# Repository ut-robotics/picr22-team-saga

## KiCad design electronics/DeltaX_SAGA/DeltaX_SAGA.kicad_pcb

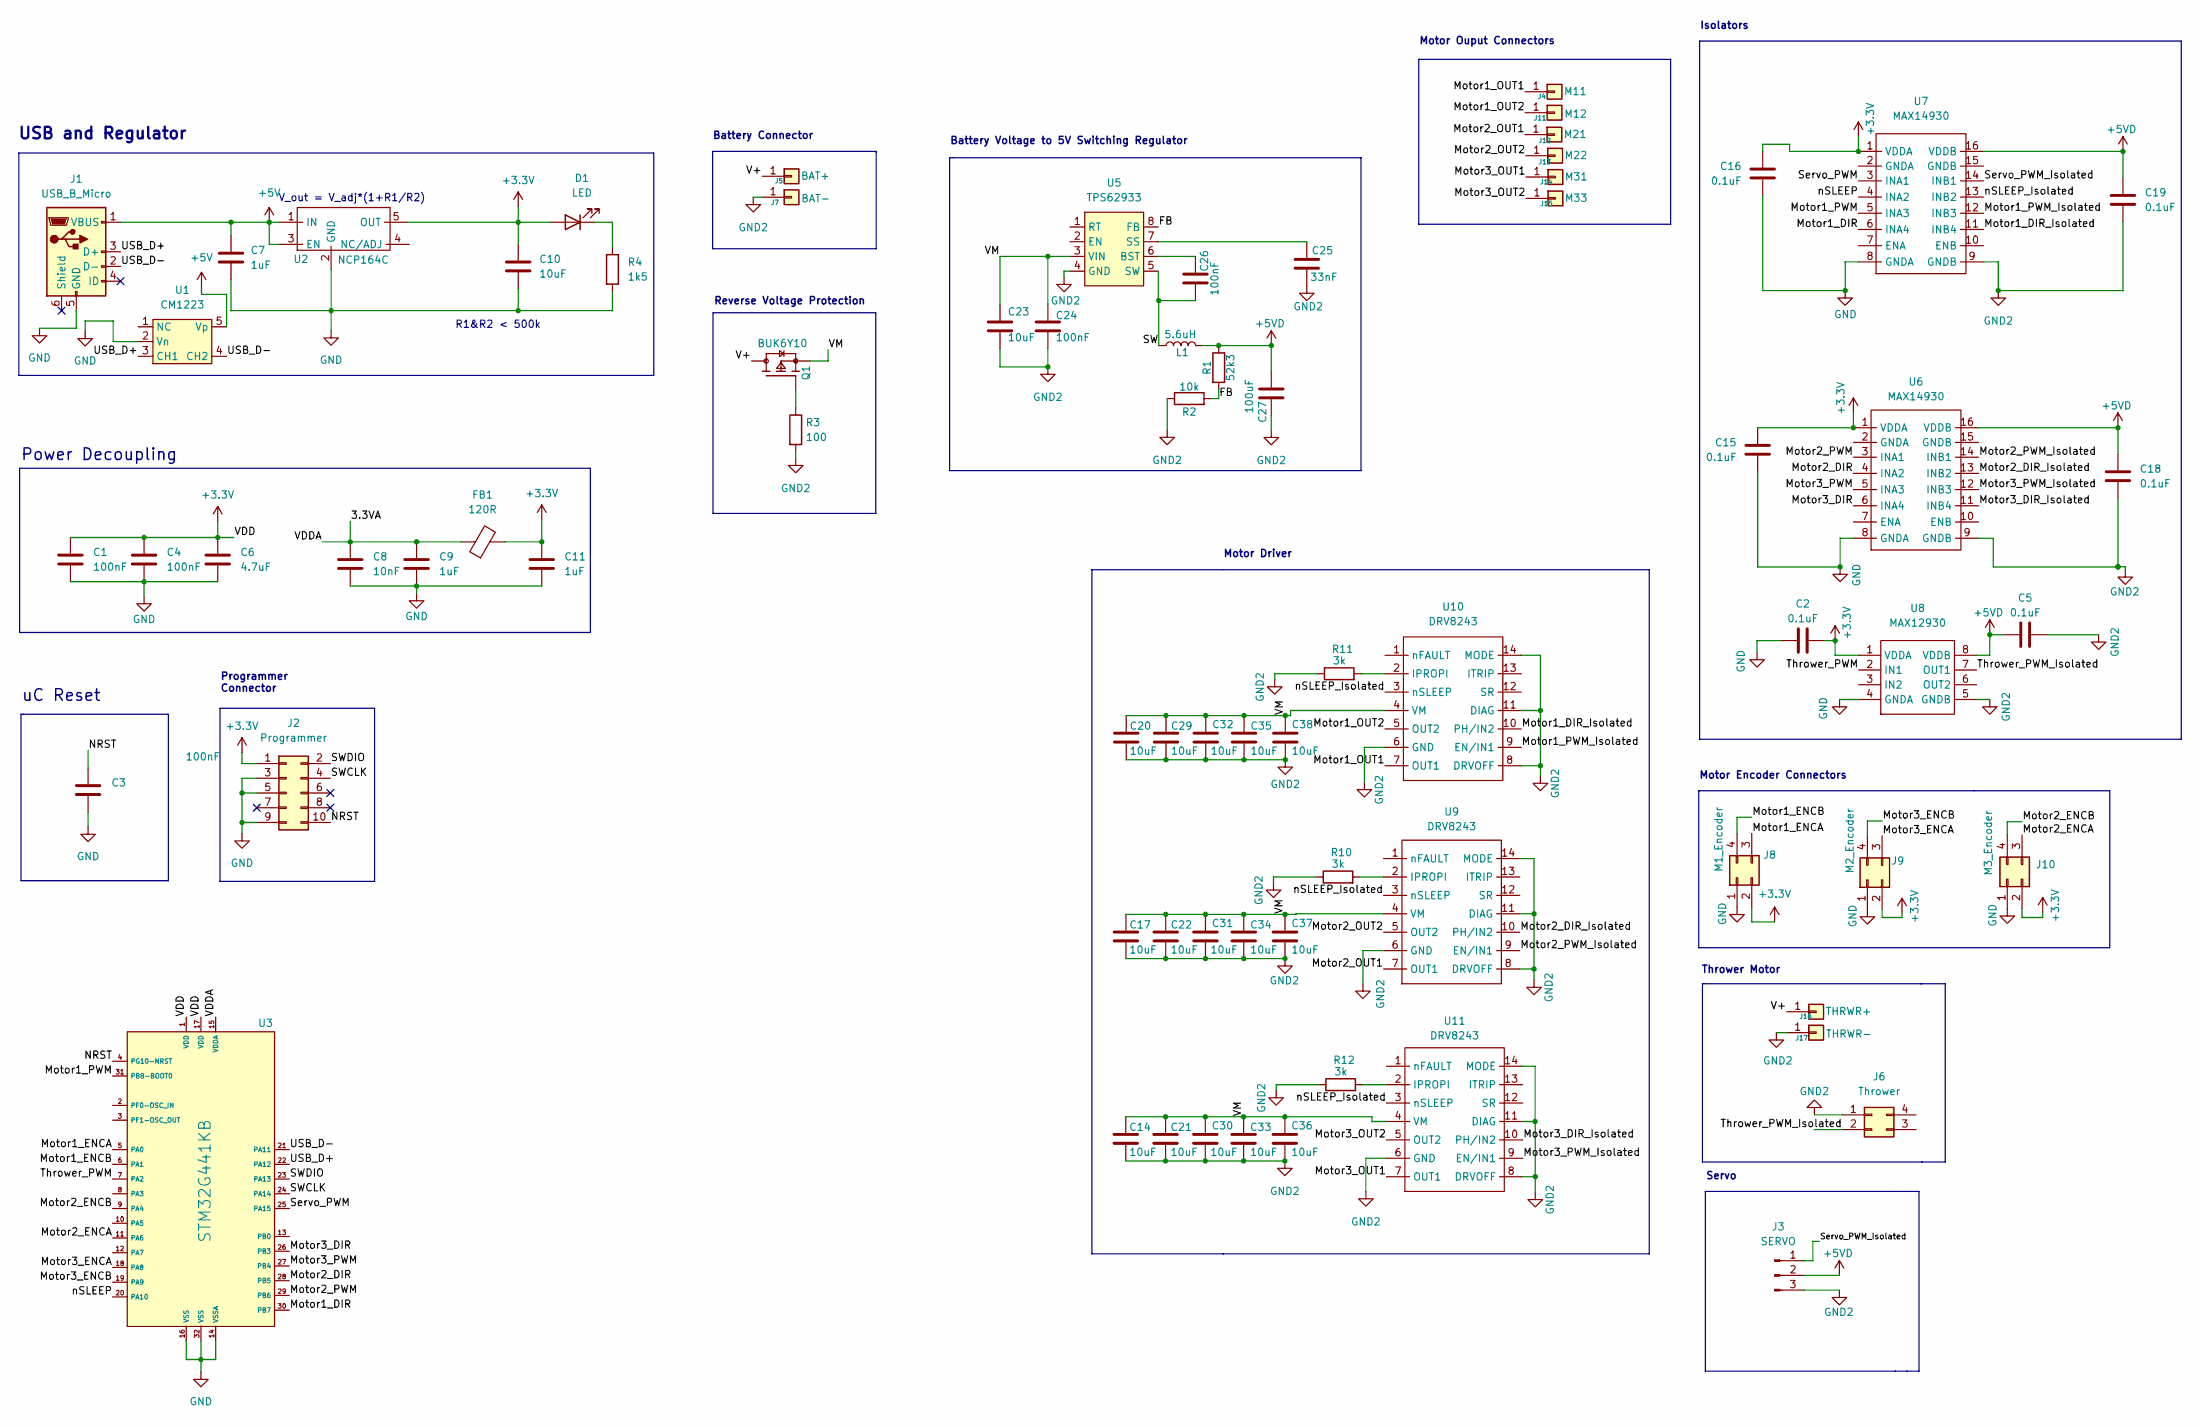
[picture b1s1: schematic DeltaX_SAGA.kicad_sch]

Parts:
C1, C3, C4, C24, C26: 100nF; C_0603_1608Metric
C2, C5, C15, C16, C18, C19: 0.1uF; C_0603_1608Metric
C6: 4.7uF; C_0603_1608Metric
C7, C9, C11: 1uF; C_0603_1608Metric
C8: 10nF; C_0603_1608Metric
C10, C14, C17, C20, C21, C22, C23, C29, C30, C31, C32, C33, C34, C35, C36, C37, C38: 10uF; C_0805_2012Metric
C25: 33nF; C_0603_1608Metric
C27: 100uF; C_1206_3216Metric
D1: LED; LED_0603_1608Metric
FB1: 120R; L_0603_1608Metric
J1: USB_B_Micro; FCI_10118193-0001LF
J2: Programmer; SAMTEC_FTSH-105-XX-X-DV
J3: SERVO; PinHeader_1x03_P2.54mm_Vertical
J4: M11; 1PinSMD
J5: BAT+; 1PinSMD
J6: Thrower; TE_7-215079-4
J7: BAT-; 1PinSMD
J8: M1_Encoder; TE_7-215079-4
J9: M2_Encoder; TE_7-215079-4
J10: M3_Encoder; TE_7-215079-4
J11: M12; 1PinSMD
J12: M21; 1PinSMD
J13: M22; 1PinSMD
J14: M31; 1PinSMD
J15: M33; 1PinSMD
J16: THRWR+; 1PinSMD
J17: THRWR-; 1PinSMD
L1: 5.6uH; SRP6060FA5R6M
Q1: BUK6Y10; TO127P600X120-5N
R1: 52k3; R_0603_1608Metric
R2: 10k; R_0603_1608Metric
R3: 100; R_0603_1608Metric
R4: 1k5; R_0603_1608Metric
R10, R11, R12: 3k; R_0603_1608Metric
U1: CM1223; SOT95P280X145-5N
U2: NCP164C; SOP95P275X110-5N
U3: STM32G441KB
U5: TPS62933
U6, U7: MAX14930; MAX14930DASE+
U8: MAX12930; MAX12930EASA+
U9, U10, U11: DRV8243

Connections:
+3.3V: C1.1, C2.2, C4.1, C6.1, C10.1, C11.1, C15.2, C16.2, D1.2 (A), FB1.2, J2.1, J8.2, J9.2, J10.2, U2.5 (OUT), U3.1 (VDD), U3.17 (VDD), U6.1 (VDDA), U7.1 (VDDA), U8.1 (VDDA)
+5V: C7.1, J1.1 (VBUS), U1.5 (Vp), U2.1 (IN), U2.3 (EN)
+5VD: C5.1, C18.2, C19.2, C27.2, J3.2, L1.2, R1.1, U6.16 (VDDB), U7.16 (VDDB), U8.8 (VDDB)
/3.3VA: C8.1, C9.1, FB1.1, U3.15 (VDDA)
/FB: R1.2, R2.2, U5.8 (FB)
/Motor1_DIR: U3.30 (PB7), U7.6 (INA4)
/Motor1_DIR_Isolated: U7.11 (INB4), U10.10 (PH/IN2)
/Motor1_ENCA: J8.3, U3.5 (PA0)
/Motor1_ENCB: J8.4, U3.6 (PA1)
/Motor1_OUT1: J4.1, U10.7 (OUT1)
/Motor1_OUT2: J11.1, U10.5 (OUT2)
/Motor1_PWM: U3.31 (PB8-BOOT0), U7.5 (INA3)
/Motor1_PWM_Isolated: U7.12 (INB3), U10.9 (EN/IN1)
/Motor2_DIR: U3.28 (PB5), U6.4 (INA2)
/Motor2_DIR_Isolated: U6.13 (INB2), U9.10 (PH/IN2)
/Motor2_ENCA: J10.3, U3.11 (PA6)
/Motor2_ENCB: J10.4, U3.9 (PA4)
/Motor2_OUT1: J12.1, U9.7 (OUT1)
/Motor2_OUT2: J13.1, U9.5 (OUT2)
/Motor2_PWM: U3.29 (PB6), U6.3 (INA1)
/Motor2_PWM_Isolated: U6.14 (INB1), U9.9 (EN/IN1)
/Motor3_DIR: U3.26 (PB3), U6.6 (INA4)
/Motor3_DIR_Isolated: U6.11 (INB4), U11.10 (PH/IN2)
/Motor3_ENCA: J9.3, U3.18 (PA8)
/Motor3_ENCB: J9.4, U3.19 (PA9)
/Motor3_OUT1: J14.1, U11.7 (OUT1)
/Motor3_OUT2: J15.1, U11.5 (OUT2)
/Motor3_PWM: U3.27 (PB4), U6.5 (INA3)
/Motor3_PWM_Isolated: U6.12 (INB3), U11.9 (EN/IN1)
/NRST: C3.1, J2.10, U3.4 (PG10-NRST)
/SW: C26.2, L1.1, U5.5 (SW)
/SWCLK: J2.4, U3.24 (PA14)
/SWDIO: J2.2, U3.23 (PA13)
/Servo_PWM: U3.25 (PA15), U7.3 (INA1)
/Servo_PWM_Isolated: J3.1, U7.14 (INB1)
/Thrower_PWM: U3.7 (PA2), U8.2 (IN1)
/Thrower_PWM_Isolated: J6.2, U8.7 (OUT1)
/USB_D+: J1.3 (D+), U1.3 (CH1), U3.22 (PA12)
/USB_D-: J1.2 (D-), U1.4 (CH2), U3.21 (PA11)
/V+: J5.1, J16.1, Q1.5 (D)
/VM: C14.1, C17.1, C20.1, C21.1, C22.1, C23.1, C24.1, C29.1, C30.1, C31.1, C32.1, C33.1, C34.1, C35.1, C36.1, C37.1, C38.1, Q1.1 (S), Q1.2, Q1.3, U5.3 (VIN), U9.4 (VM), U10.4 (VM), U11.4 (VM)
/nSLEEP: U3.20 (PA10), U7.4 (INA2)
/nSLEEP_Isolated: U7.13 (INB2), U9.3 (nSLEEP), U10.3 (nSLEEP), U11.3 (nSLEEP)
GND: C1.2, C2.1, C3.2, C4.2, C6.2, C7.2, C8.2, C9.2, C10.2, C11.2, C15.1, C16.1, J1.5 (GND), J2.3, J2.5, J2.9, J8.1, J9.1, J10.1, R4.2, U1.2 (Vn), U2.2 (GND), U3.14 (VSSA), U3.16 (VSS), U3.32 (VSS), U6.8 (GNDA), U7.8 (GNDA), U8.4 (GNDA)
GND2: C5.2, C14.2, C17.2, C18.1, C19.1, C20.2, C21.2, C22.2, C23.2, C24.2, C25.2, C27.1, C29.2, C30.2, C31.2, C32.2, C33.2, C34.2, C35.2, C36.2, C37.2, C38.2, J3.3, J6.1, J7.1, J17.1, R2.1, R3.2, R10.1, R11.1, R12.1, U5.4 (GND), U6.9 (GNDB), U7.9 (GNDB), U8.5 (GNDB), U9.6 (GND), U9.8 (DRVOFF), U9.11 (DIAG), U9.14 (MODE), U10.6 (GND), U10.8 (DRVOFF), U10.11 (DIAG), U10.14 (MODE), U11.6 (GND), U11.8 (DRVOFF), U11.11 (DIAG), U11.14 (MODE)
unnamed: C25.1, U5.7 (SS)
unnamed: C26.1, U5.6 (BST)
unnamed: D1.1 (K), R4.1
unnamed: Q1.4 (G), R3.1
unnamed: R10.2, U9.2 (IPROPI)
unnamed: R11.2, U10.2 (IPROPI)
unnamed: R12.2, U11.2 (IPROPI)

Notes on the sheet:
Power Decoupling
Isolators
USB and Regulator
Motor Driver
Servo
Motor Encoder Connectors
Reverse Voltage Protection
uC Reset
Battery Connector
Battery Voltage to 5V Switching Regulator
R1&R2 < 500k
Motor Ouput Connectors
V_out = V_adj*(1+R1/R2)
Thrower Motor
Programmer Connector

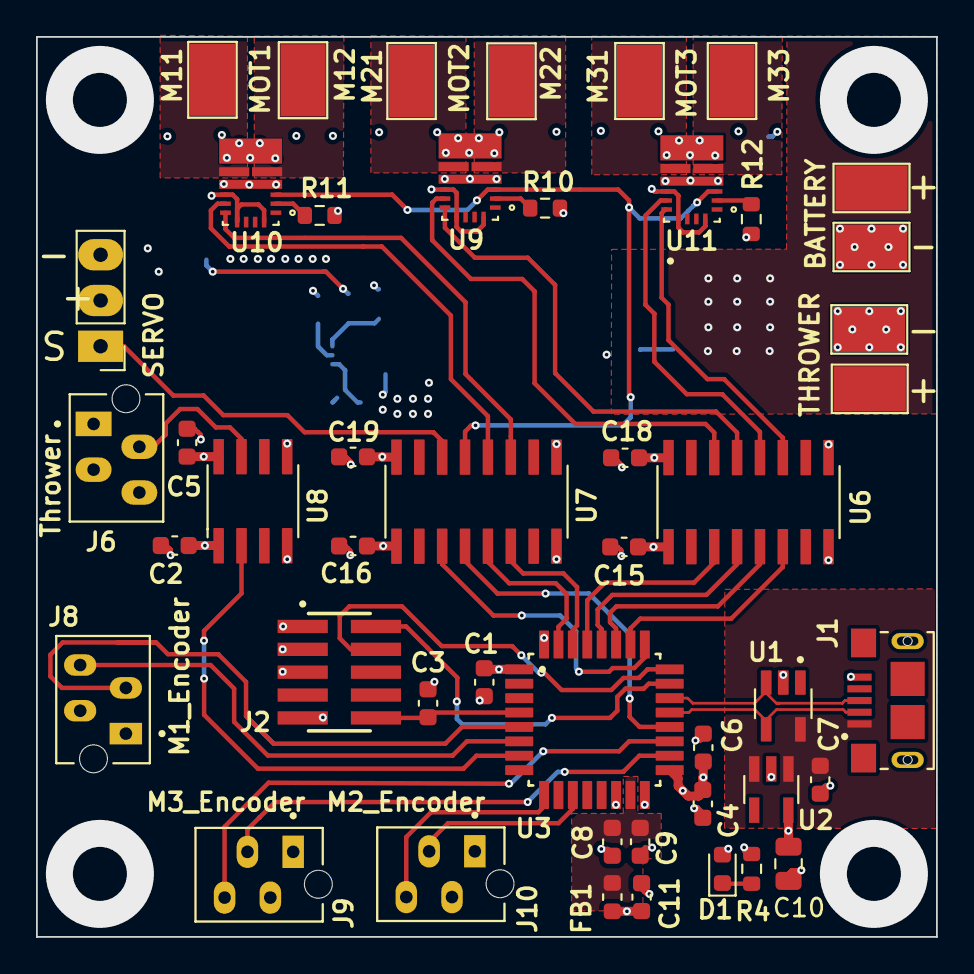
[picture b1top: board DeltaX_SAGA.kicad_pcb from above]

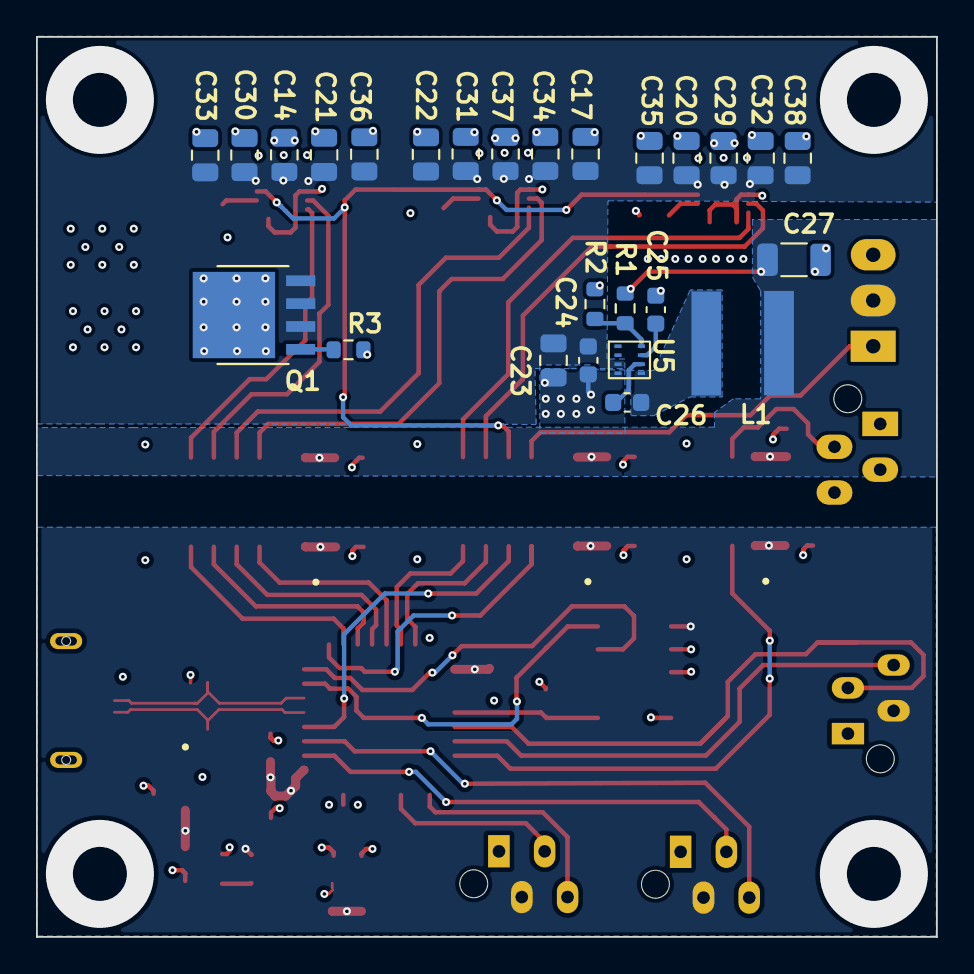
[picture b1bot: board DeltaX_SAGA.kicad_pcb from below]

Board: 4 copper layers, 50.0 x 50.0 mm, 73 parts (30 on the bottom side), 52 nets.

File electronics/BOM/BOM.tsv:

Name	Designator	Quantity	Description	Mouser Order Code	Farnell Order Code	TME Order Code
10nF	C8	1	Multilayer Ceramic Capacitors MLCC - SMD/SMT CGA 0603 50V 0.01uF X7R 10% AEC-Q200	810-CGA3E2X7R1H103K	CA07638	N/A
33nF	C25	1	Multilayer Ceramic Capacitors MLCC - SMD/SMT 0402 50VDC 0.033uF 10% X7R	963-MAASU105SB7333KF	1740618	06035C333JAT2A
100nF	C1, C3, C4, C24, C26	5	Multilayer Ceramic Capacitors MLCC - SMD/SMT 0402 50VDC 0.1uF 10% X7R AEC-Q200	963-UMK105B7104KVHF	0603B104J500CT	2332586
0.1uF	C2, C5, C15, C16, C18, C19	6	Multilayer Ceramic Capacitors MLCC - SMD/SMT 0402 50VDC 0.1uF 10% X7R AEC-Q200	963-UMK105B7104KVHF	CC0603KRX7R8BB104	1740614
4.7uF	C6	1	Multilayer Ceramic Capacitors MLCC - SMD/SMT 0603 10VDC 4.7uF 10% X7T AEC-Q200	810-CGA3E1X7T1A475AC	N/A	N/A
10uF	C10, C14, C17, C20, C21, C22, C23, C29, C30, C31, C32, C33, C34, C35, C36, C37, C28	17	Multilayer Ceramic Capacitors MLCC - SMD/SMT 10uF, 25V, 10%, X6S, 0805 Multi-layer Ceramic Capacitor	187-CL21X106KAYQNWE	C2012X5R1E106KAB	2346927
100uF	C27	1	Multilayer Ceramic Capacitors MLCC - SMD/SMT 1206 6.3VDC 100uF 20% X5R	963-JMK316BJ107ML-T	3922223	N/A
LED	D1	1	LED Uni-Color Green 565nm 2-Pin Chip LED T/R, LED GREEN CLEAR CHIP SMD	859-LTST-C190GKT	LTST-C190GKT	1465991
120R	FB1	1	Ferrite Beads BMC 0603 120R 25% A Gen C	279-BMC1JY0120AN	N/A	N/A
USB_B_Micro	J1	1	USB - micro B USB 2.0 Receptacle Connector 5 Position Surface Mount, Right Angle; Through Hole	649-10118193-0001LF	10118193-0001LF/C	2751675
Programmer	J2	1	Detachable Programmer connector	200-FTSH10501LDVK	N/A	N/A
SERVO	J3	1	3-pin vertical header pin 2.54mm pitch	855-M20-9770446	CN21901	N/A
M1_Encoder	J8	1	PCB Receptacle, Board-to-Board, 1.27 mm, 2 Rows, 4 Contacts, Through Hole Mount, Micro-MaTch	571-215079-4	1772996	7-215079-4
M2_Encoder	J9	1	PCB Receptacle, Board-to-Board, 1.27 mm, 2 Rows, 4 Contacts, Through Hole Mount, Micro-MaTch	571-215079-4	1772996	7-215079-4
M3_Encoder	J10	1	PCB Receptacle, Board-to-Board, 1.27 mm, 2 Rows, 4 Contacts, Through Hole Mount, Micro-MaTch	571-215079-4	1772996	7-215079-4
Thrower	J6	1	PCB Receptacle, Board-to-Board, 1.27 mm, 2 Rows, 4 Contacts, Through Hole Mount, Micro-MaTch	571-215079-4	1772996	7-215079-4
5.6 uH	L1	1	Power Inductor (SMD), 5.6 µH, 10 A, Shielded, 10 A, SRP6060FA	652-SRP6060FA-5R6M	2901832	N/A
BUK6Y10	Q1	1	BUK6Y10-30P	771-BUK6Y10-30PX	BUK6Y10-30PX	3438512
100	R3	1	Thick Film Resistors - SMD 100 Ohms 200 mW 0603 5%	603-RC0603JR-7W100RL	N/A	N/A
1k5	R4	1	Thick Film Resistors - SMD 1/10watt 1.5Kohms 5%	71-CRCW0603J-1.5K-E3	N/A	0603SAF1501T5E
3k	R10, R11, R12	3	Chip Resistor, 0 Ohm, Jumper, 100 mW, -55 to 155 degC, 0603 (1608 Metric), RoHS, Tape and Reel	667-ERJ-UP3F3301V	ERA3AEB332V	9238549
10k	R3	1	Chip Resistor, 0 Ohm, Jumper, 100 mW, -55 to 155 degC, 0603 (1608 Metric), RoHS, Tape and Reel	603-RT0603FRE0710KL	CRGP0603F10K	2073356
52k3	R1 	1	52.3 kOhm, SMD 0603	667-ERJ-3EKF5232V	2059474	ERJ3EKF5232V
CM1223	U1	1	Industry First Low Capacitance ESD Protection Arrays with Backdrive Protection, 5-Pin SOT- 23	748-CM1223-02SO	3607672	CM1223-02SO
NCP164C	U2	1	LDO Voltage Regulators LDO 300mA AD 3.3V	863-NCP164CSN330T1G	3367831	NCP164CSN330T1G
STM32G441KB	U3	1	ARM MCU, STM32 Family STM32G4 Series Microcontrollers, ARM Cortex-M4F, 32 bit, 170 MHz, 128 KB	511-STM32G441KBT6	3132413	N/A
TPS62933	U5	1	Switching Voltage Regulators 3.8-V to 30-V, 3-A, 200-kHz to 2.2-MHz, low-IQ synchronous buck converter in SOT-583 package	595-TPS62933DRLR	N/A	N/A
MAX14930	U6, U7	1	Digital Isolator, 4 Channel, 38.2 ns, 1.71 V, 5.5 V, NSOIC, 16 Pins	700-MAX14930AASE+	3918113	N/A
MAX12930	U8	1	Digital Isolator, 2 Channel, 23.9 ns, 1.71 V, 5.5 V, NSOIC, 8 Pins	700-MAX12930EASA+	3918086	N/A
DRV8243	U9, U10, U11	3	Automotive 40-V, 12-A H-Bridge driver with integrated current sensing and feedback 14-VQFN-HR -40 to 125	595-DRV8243HQRXYRQ1	N/A	N/A

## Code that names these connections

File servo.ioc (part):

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Mcu.Name=STM32G431K(6-8-B)Tx
Mcu.Package=LQFP32
Mcu.UserName=STM32G431KBTx
PA0.GPIOParameters=GPIO_Label
PA0.GPIO_Label=M1_ENCA
PA0.Signal=S_TIM2_CH1
PA1.GPIOParameters=GPIO_Label
PA1.GPIO_Label=M1_ENCB
PA1.Signal=S_TIM2_CH2
PA10.GPIOParameters=GPIO_Label
PA10.GPIO_Label=nSleep
PA10.Signal=GPIO_Output
PA11.Mode=Device
PA11.Signal=USB_DM
PA12.Mode=Device
PA12.Signal=USB_DP
PA13.GPIOParameters=GPIO_Label
PA13.GPIO_Label=T_SWDIO
PA13.Mode=Serial_Wire
PA13.Signal=SYS_JTMS-SWDIO
PA14.GPIOParameters=GPIO_Label
PA14.GPIO_Label=T_SWCLK
PA14.Mode=Serial_Wire
PA14.Signal=SYS_JTCK-SWCLK
PA15.GPIOParameters=GPIO_Label
PA15.GPIO_Label=Servo_PWM
PA15.Signal=S_TIM8_CH1
PA2.GPIOParameters=GPIO_Label
PA2.GPIO_Label=Thrower_PWM
PA2.Signal=S_TIM15_CH1
PA4.GPIOParameters=GPIO_Label
PA4.GPIO_Label=M2_ENCB
PA4.Signal=S_TIM3_CH2
PA6.GPIOParameters=GPIO_Label
PA6.GPIO_Label=M2_ENCA
PA6.Signal=S_TIM3_CH1
PA8.GPIOParameters=GPIO_Label
PA8.GPIO_Label=M3_ENCA
PA8.Signal=S_TIM1_CH1
PA9.GPIOParameters=GPIO_Label
PA9.GPIO_Label=M3_ENCB
PA9.Signal=S_TIM1_CH2
PB3.GPIOParameters=GPIO_Label
PB3.GPIO_Label=M3_DIR
PB3.Signal=GPIO_Output
PB4.GPIOParameters=GPIO_Label
PB4.GPIO_Label=M3_PWM
PB4.Signal=S_TIM16_CH1
PB5.GPIOParameters=GPIO_Label
PB5.GPIO_Label=M2_DIR
PB5.Signal=GPIO_Output
PB6.GPIOParameters=GPIO_Label
PB6.GPIO_Label=M2_PWM
PB6.Signal=S_TIM4_CH1
PB7.GPIOParameters=GPIO_Label
PB7.GPIO_Label=M1_DIR
PB7.Signal=GPIO_Output
PB8-BOOT0.GPIOParameters=GPIO_Label
PB8-BOOT0.GPIO_Label=M1_PWM
PB8-BOOT0.Signal=S_TIM4_CH3
PF0-OSC_IN.GPIOParameters=GPIO_Label
PF0-OSC_IN.GPIO_Label=M1_DIR_1
PF0-OSC_IN.Signal=GPIO_Output
PF1-OSC_OUT.GPIOParameters=GPIO_Label
PF1-OSC_OUT.GPIO_Label=M1_DIR_2
PF1-OSC_OUT.Signal=GPIO_Output
RCC.HSE_VALUE=8000000
RCC.SYSCLKFreq_VALUE=160000000
RCC.SYSCLKSource=RCC_SYSCLKSOURCE_PLLCLK
board=NUCLEO-G431KB
boardIOC=true

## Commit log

2022-09-07 Initialize software
2022-09-07 Initialize documentation
2022-09-07 Initialize firmware
2022-09-07 Initialize electronics
2022-09-11 initial schematic design(without thrower)
2022-09-11 design of necessary symbols
2022-09-11 screenshot of the schematic design till date
2022-09-11 initial schematic updated
2022-09-11 screenshot of updated schematic added
2022-09-11 backups for schematic added
2022-09-15 schematic updated
2022-09-15 new symbol libraries added
2022-09-15 backup files added
2022-09-15 schematic annotated and some components assigned
2022-09-15 renamed the schematic library directory
2022-09-15 Footprint libaries directory created with necessary footprints
2022-09-15 previous unnecessary files removed
2022-09-15 motor driver footprint added
2022-09-18 updated the team page and blog from my side
2022-09-18 updated the boardc schematic and pcb design
2022-09-18 libraries updated
2022-09-18 team page updated
2022-09-18 updated the readme file
2022-09-18 added backup files
2022-09-18 README from this branch omitted
2022-09-19 team page with blog added
2022-09-29 Schematic board updated
2022-09-29 PCB design updated
2022-09-29 PCB dsign updated
2022-09-29 cache
2022-09-29 PCB design updated with fill zones
2022-09-30 Updated library for DRV8243
2022-09-30 Updated library MAX12930
2022-09-30 Updated library for MAX14930
2022-09-30 Updated library for NCP164C
2022-09-30 Updated PCB board
2022-09-30 added cache files
2022-09-30 Added the backup files
2022-09-30 PCB updated
2022-10-03 Board schematic updated
2022-10-03 added library for buck TPS62933
2022-10-03 Updated the PCB design
2022-10-03 Updated kicad files
2022-10-03 added chache files
2022-10-03 added lib-table
2022-10-03 backup file added
2022-10-03 daily log added
2022-10-10 updated the reverse voltage MSOFET footprint library
2022-10-10 added footprint library for the inductor SRP6060FA5RM
2022-10-10 updated the kicad schematic symbol for the MSOFET
2022-10-10 Updated the schematic
2022-10-10 Updated the KiCAD package
2022-10-10 updated the KiCAD prl file
2022-10-10 updated the library table
2022-10-10 Updated the symbol for TPS62933 buck
2022-10-11 complete PCB updated
2022-10-11 added a single pin solderable pad
2022-10-12 PCB design updated and complete design added
2022-10-12 updated PCB design
2022-10-13 KiCAD package updated
2022-10-13 Reverse Voltage Protection MOSFET PCB footprint updated
2022-10-17 PCB board updated
2022-10-17 updated the kciad project file
2022-10-17 Team blog from my side updated
2022-10-20 KiCAD package/s updated
2022-10-20 Footprint libraries updated
2022-10-23 Updated the PDB design
2022-10-23 KiCAD project files updated
2022-10-23 Full PCB design updated
2022-10-23 KiCAD project files added
2022-10-26 KiCAD project file updated
2022-10-26 Backup files addde
2022-10-27 PCB design added
2022-10-27 KiCAD project file/s added
2022-10-27 KiCAD files added
2022-10-27 Labels and orientations of certain components updated in schematic
2022-10-27 PCB labels updated
2022-10-28 PCB design with label optimised and updated
2022-10-28 PCB labels and routing optimised and updated
2022-10-28 PCB design updated with labels aligned
2022-10-28 KiCAD project file updatde
2022-10-30 PCB design updated with routing improvements
2022-10-30 PCB design updated with improved routing
2022-10-31 Updated PCB design with board cutouts and holes in proper grid size
2022-10-31 Updated PCB design with gerbers
2022-10-31 Gerber files added
2022-10-31 Team blog added from my(Anish) side
2022-10-31 PCB design updated with correct labels
2022-11-14 previously pads not connected reviewed and updated
2022-11-14 BNackup files added
2022-11-14 updated the team documentation README.asciidoc
2022-11-14 updated the team documentation
2022-12-08 directory boilerplate files
2022-12-08 instances for camera api and test files added
2022-12-08 enum class for color for specific objects added
2022-12-08 python code for configuring color for various objects added
2022-12-08 pythin aoi for image processing added
2022-12-08 api.py file for driving motors and thrower methods added
2022-12-08 requirements.txt added
2022-12-08 code for task: mainboard communication added
2022-12-08 code for streaming video from the camer added
2022-12-08 code for the task: find a ball added
2022-12-08 code for the task: follow a ball added
2022-12-10 python setup removed
2022-12-10 requirements file removed
2022-12-12 removed unnecessary files
2022-12-12 Finding a serial port code added
2022-12-12 updated with the new api.py file for serial port finding
2022-12-12 updated the code fetching the frame size from camera object
2022-12-12 variable nomenclature made consitent
2022-12-12 raise exception when USB com port not found
2022-12-12 states for state machine logic
2022-12-12 updated the USB port dynamic search
2022-12-12 updated the code with frame size from camera object
2022-12-12 added testing state machine for manual mode
2022-12-12 enum class with states added
2022-12-12 testing the state machine implementation
2022-12-12 added the progress and team documentation from my side
2022-12-12 updated the mainboard communication with state machine implementation
2022-12-12 updated the dynamic searching of the USB device
2022-12-12 changed the largest ball variable using already sorted processed_ball from image_processor
2022-12-12 updated the iamge processor file
2022-12-12 updated the mainboard communication program withs tate machine logic to drive forward on speed commands
2022-12-12 added the incomplete code for finding and following the ball using state machine logic
2022-12-12 updated the code with try except block
2022-12-12 initial
2022-12-12 updated the largest processed ball with alerady sorted list from image processor
2022-12-13 state machine functions added
2022-12-13 main file for all taks combnined
2022-12-13 finding the ball program updated
2022-12-13 video streaming program wiht the largest ball fetched from processed data list without max filtering
2022-12-13 main program with the largest ball fetched from processed data list without max filtering
2022-12-13 state machine logic implementation with updated ball location for following
2022-12-13 added the function to turn when there is no ball
2022-12-13 updated the code removing assigning states and calls functions from state_machine.py
2022-12-13 refactored the code ommiting the redundant codes
2022-12-13 updated the state machine code which takes the entire processed data as input
2022-12-13 updated the code to send entire processed data frame as input to state machine code
2022-12-13 passed the frame resolution ubsing the camera object
2022-12-13 updated the current state function with frame resolution passed from main.py
2022-12-13 passed the camera resolution parameters in the constructor class of the state machine call
2022-12-13 updated the state machine code with camera resolution parameters in the constructor
2022-12-13 minor tweaks
2022-12-15 fixes and add PID back propagation control
2022-12-16 fix PID
2022-12-21 code cleanup
2022-12-21 cmake bug fix
2022-12-21 commented code remover
2022-12-21 fix for new robot change 1 and 3 encoders
2023-01-13 BOM file added
2023-01-13 schematic PDF added
2023-01-13 PCB 3D views with annotations and labels added
2023-01-13 electronics documentation updated
2023-01-13 front PCB image updated
2023-01-14 software documentation added
2023-01-14 software documentation updated
2023-01-14 added section frames for documentation
2023-01-14 PCB front and back 3D images with annotations and labels added
2023-01-14 Electronics Design documentation added
2023-01-14 PCB images front and back with annotations and labels
2023-01-14 removinf unnecessary files
2023-01-14 flow chart added
2023-01-14 programming documentation updated with flow charts
2023-01-14 programming documentation updated
2023-01-14 added all necessary images
2023-01-14 Team documentation updated
2023-01-14 removed few images
2023-01-14 PCB front and back 3D view added
2023-01-14 added mechanics pictures
2023-01-14 replacing the state machine logic
2023-01-14 updated the robot states with DRIVE_TO_OTHER_HALF state
2023-01-14 updated the state machine logic with an additional state of driving to other half
2023-01-14 updated mechanics readme
2023-01-14 updated the electronics documentation
2023-01-14 removing redundant files
2023-01-14 updated the mechanics documentation
2023-01-14 updated team documentation
2023-01-14 removing outdated state machine flow chart
2023-01-14 added the updated state machine flow chart
2023-01-14 added fusion assembly link
2023-01-14 removing outdated state machine work flow
2023-01-14 fusion assembly link
2023-01-14 added the new state machine work flow
2023-01-14 removing the outdated state machine work flow
2023-01-14 updated state_machine_workflow added
2023-01-14 updated the team documentation with updated state machine logic
2023-01-14 added self analysis
2023-01-14 updated personal comments
2023-01-14 fixed formatting issues
2023-01-14 electronics documentation added
2023-01-14 removed previous BOM
2023-01-14 updated the BOM
2023-01-15 Team documentation updated correcting issues
2023-01-15 added software/README inside the software folder
2023-01-15 removinf README from root
2023-01-15 updated software documentation
2023-01-15 firmware/README added with format and description of data
2023-01-15 Team documentation updated with the ew robot's image in Mechanics section
2023-01-15 electronics documentation moved in correct directory
2023-01-15 removing previous copy
2023-01-15 documentation updated
2023-01-15 updated IPROPI resistor value
2023-01-15 replacing old schematic
2023-01-15 updated pdf for schematic added
2023-01-15 removing old BOM
2023-01-15 new BOM added
2023-01-16 BOM file updated
2023-01-17 added updated codes to BOM
2023-01-18 updated valid and relevant codes as per the previous comments
